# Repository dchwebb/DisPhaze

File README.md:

# Dis Phaze

Eurorack module providing two Phase Distortion oscillators based on Casio's CZ synthesizors. 

Phase distortion involves warping a sine wave using a second phase distortion signal. The phase distortion tables in this module were loosely based on waveforms sampled from a Casio CZ-1000. Both oscillators allow the sine wave to be warped by a greater amount than on the original and in the case of oscillator 1 the phase distortion tables can be continuously varied.

Functionality
-------------

Disphaze is a two channel design where each channel controls 5 phase distortion waves. These are used to change the playback rate of the audio wave which is always a sine wave. All of the PD waves are based on the CZ but some are generated mathematically, some literally sampled and converted from an original CZ-1000.

The module is duophonic – channel one has a bit more range and so can go more extreme than the CZ. Channel one allows the PD waves morph from one to the next. The second channel does not morph and has a more limited range so it is a bit more 'authentic'. Channel two can also be offset by an octave from channel one which is particularly useful for ring modulation. The module works well in stereo with the two channels split left and right.

Channel one has a Ring Mod switch which digitally multiplies both channel ouputs. Channel two has a mix switch which adds both channel outputs.

The amount of phase distortion applied can be controlled with a knob and/or CV input. Pitch is applied with a 1V/Octave input which is also normalled to the Doepfer standard 16 pin Eurorack connector. The module is also supplied with a VCA input - this allows the use of an envelope generator (or other CV source) to control volume without the need for an external VCA.

Calibration
-----------

 * Set fine tune and both phase distortion amount knobs to the center position
 * Connect a voltage source to the 1V/Oct input
 * Press the calibration button once (top right of back of PCB) - a square wave will be output on channel 1
 * The top left knob will adjust the tuning offset (will be affected by spread setting)
 * The top right knob will adjust the tuning spread (test by checking different octaves)
 * When the calibration is complete press the calibration button again to save

Technical
---------

The heart of the module is the STM32F405 microcontroller running at 168MHz. Timing is generated with an external 8MHz crystal oscillator. CV inputs are conditioned with an MCP6004 OpAmp. The outputs are derived from the Microcontroller's 12 bit DACs amplified via a TL072 OpAmp. The microcontroller is programmed from a 4 pin SWD header.

The module uses a two PCB sandwich construction with vertical potentiometers and jack sockets connecting the two PCBs and providing structural rigidity.
 
 Errata
 ------
 
 * On v2 of the PCB the BOOT0 pin (pin 60) is floating which causes problems programming and debugging over the SWD interface. A bodge wire connects this to ground (pin 2 of C9).
 * Silkscreen for C4 and C17 are incorrectly swapped
 * VDDA is missing decoupling capacitors
 * Reset button missing
 * USB/UART not exposed
 * No silkscreen on calibrate button

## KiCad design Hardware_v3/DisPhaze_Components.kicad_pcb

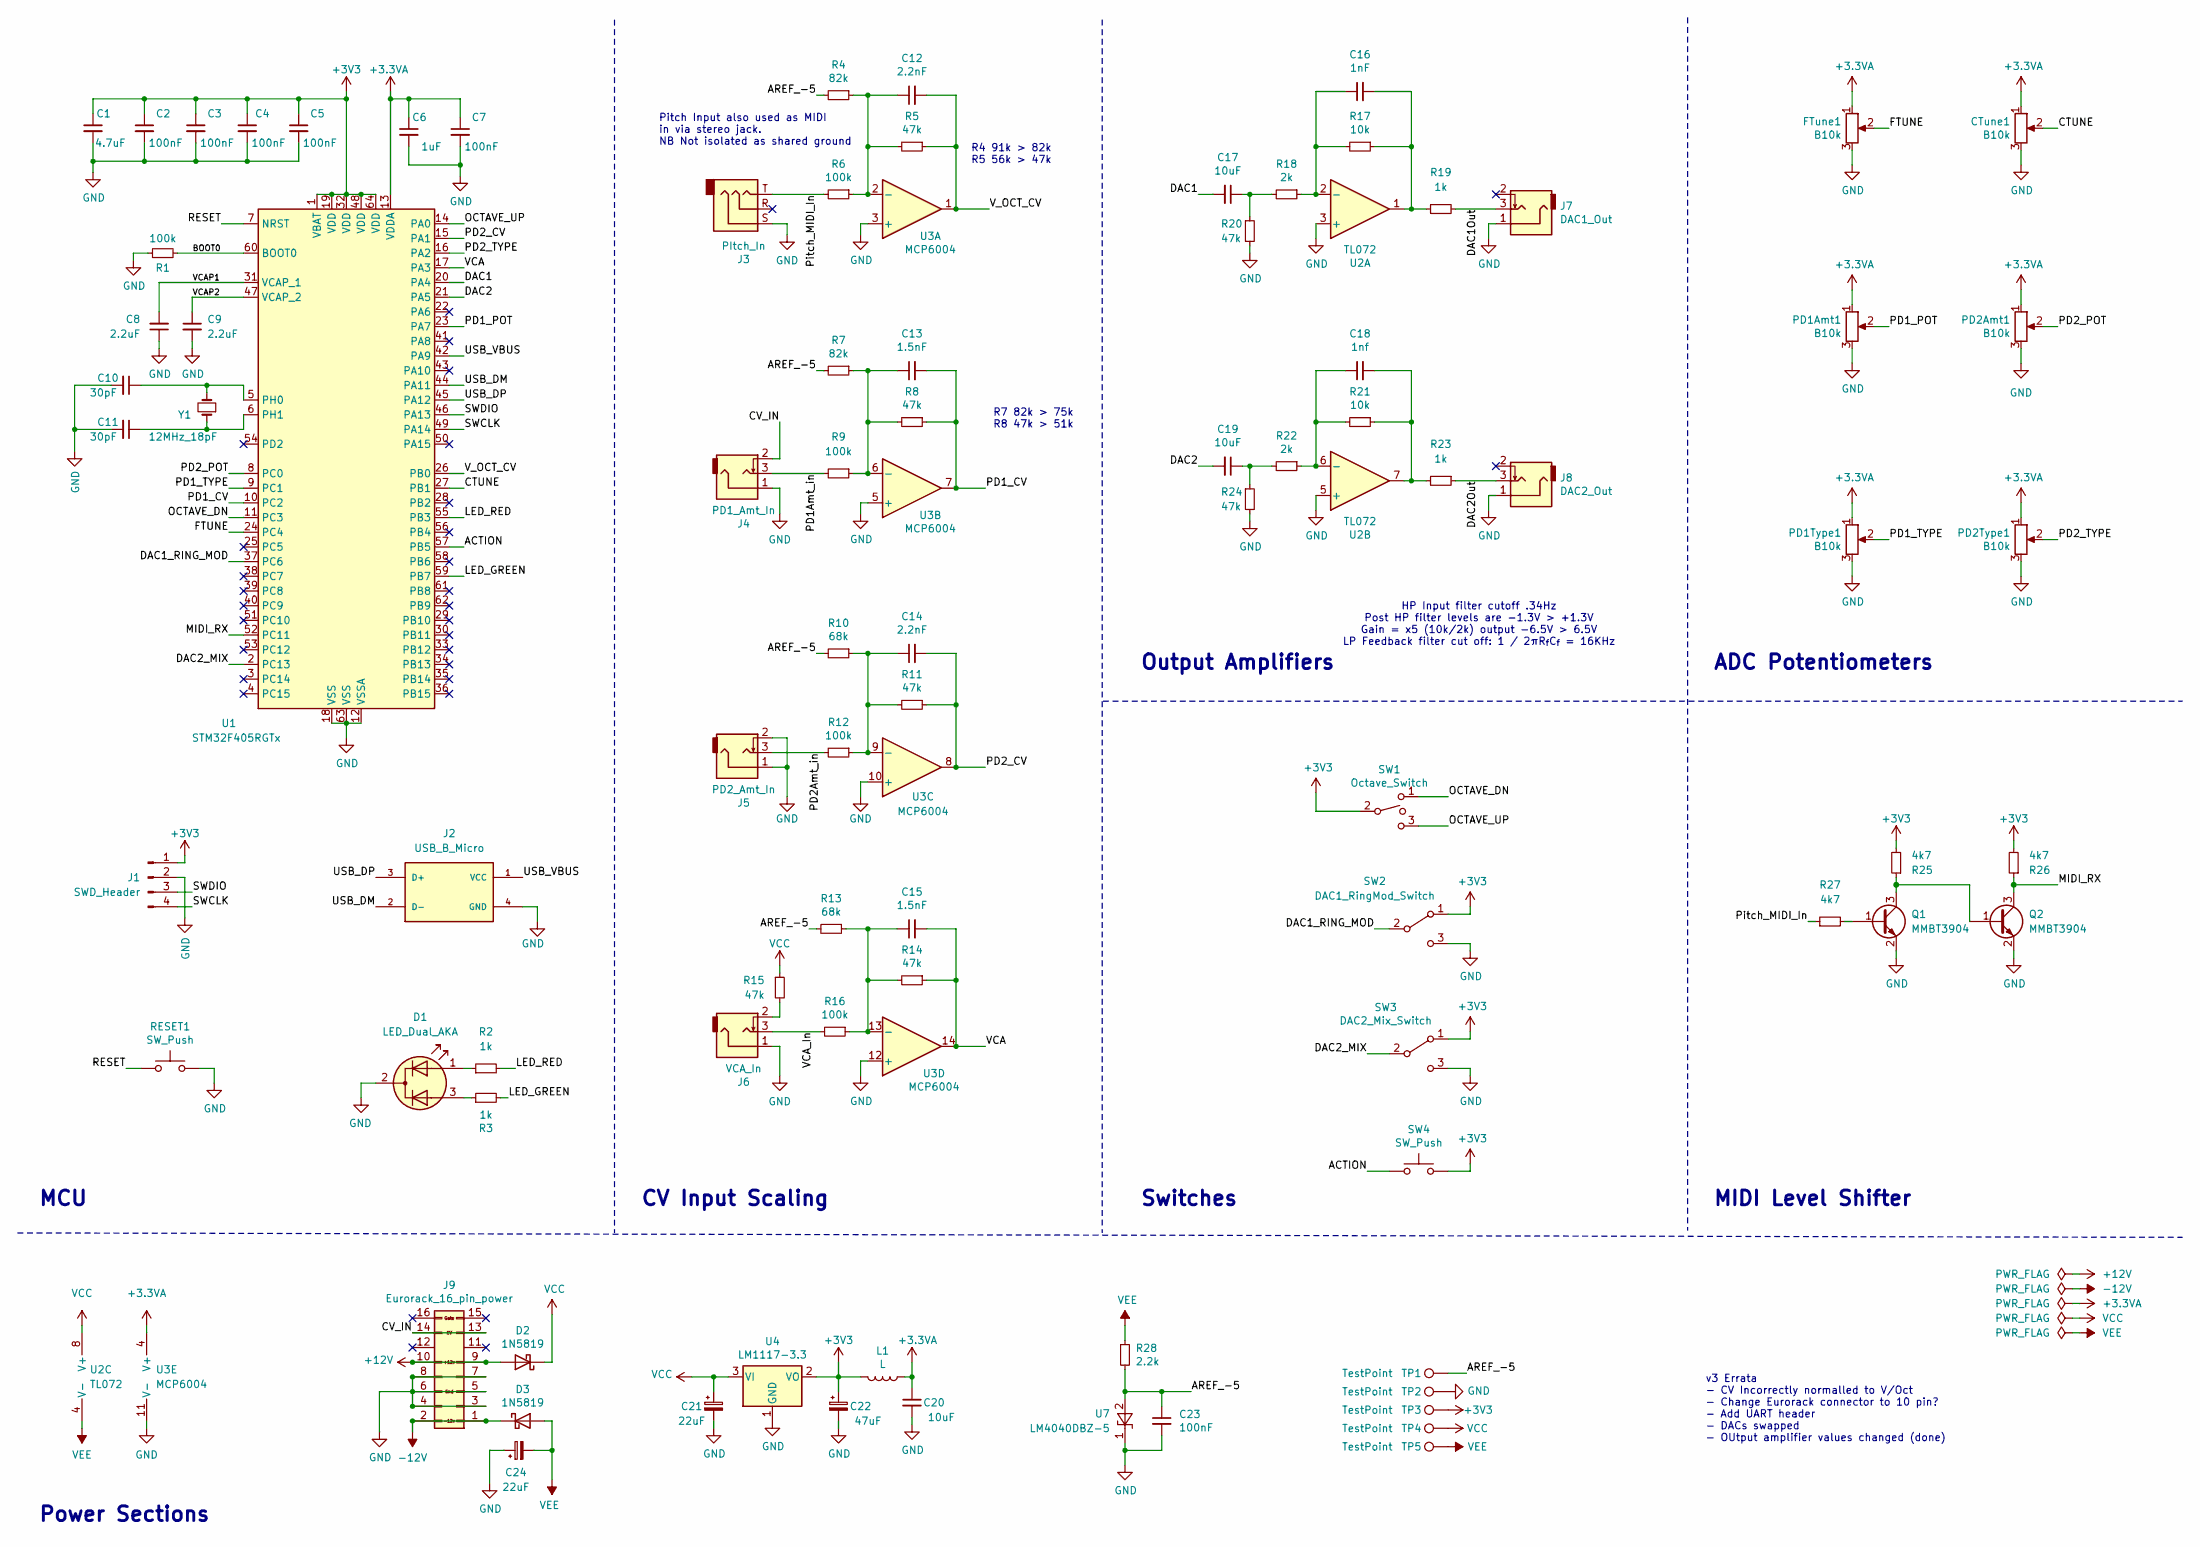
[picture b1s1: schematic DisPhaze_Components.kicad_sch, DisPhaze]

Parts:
C1: 4.7uF; C_0603_1608Metric
C2, C3, C4, C5, C7, C23: 100nF; C_0603_1608Metric
C6: 1uF; C_0603_1608Metric
C8, C9: 2.2uF; C_0603_1608Metric
C10, C11: 30pF; C_0603_1608Metric
C12, C14: 2.2nF; C_0603_1608Metric
C13, C15: 1.5nF; C_0603_1608Metric
C16: 1nF; C_0603_1608Metric
C17, C19: 10uF; C_0603_1608Metric
C18: 1nf; C_0603_1608Metric
C20: 10uF; C_0805_2012Metric
C21, C24: 22uF; CP_Elec_4x5.3
C22: 47uF; CP_Elec_5x5.4
CTune1: B10k; Alpha_9mm_Potentiometer_Aligned
D1: LED_Dual_AKA; LED_D3.0mm-3
D2, D3: 1N5819; D_SOD-123
FTune1: B10k; Alpha_9mm_Potentiometer_Aligned
J1: SWD_Header; SWD_header
J2: USB_B_Micro; USB_TE_1734517-1
J3: PItch_In; Thonkiconn_Stereo-PJ366ST
J4: PD1_Amt_In; THONKICONN_hole
J5: PD2_Amt_In; THONKICONN_hole
J6: VCA_In; THONKICONN_hole
J7: DAC1_Out; THONKICONN_hole
J8: DAC2_Out; THONKICONN_hole
J9: Eurorack_16_pin_power; Eurorack_16_pin_header
L1: L; L_0805_2012Metric
PD1Amt1, PD1Type1, PD2Amt1, PD2Type1: B10k; Alpha_9mm_Potentiometer_Aligned
Q1, Q2: MMBT3904; SOT-23; Part_Number C20526
R1: 100k; R_0603_1608Metric; Part_Number C25803
R2, R3, R19, R23: 1k; R_0603_1608Metric
R4, R7: 82k; R_0603_1608Metric
R5, R8, R11, R14, R15, R20, R24: 47k; R_0603_1608Metric
R6, R9, R12, R16: 100k; R_0603_1608Metric
R10, R13: 68k; R_0603_1608Metric
R17, R21: 10k; R_0603_1608Metric
R18, R22: 2k; R_0603_1608Metric
R25, R26, R27: 4k7; R_0603_1608Metric; Part_Number C23162
R28: 2.2k; R_0603_1608Metric
RESET1: SW_Push; SW_SPST_EVQQ2
SW1: Octave_Switch; SPDTSubMiniature
SW2: DAC1_RingMod_Switch; SPDTSubMiniature
SW3: DAC2_Mix_Switch; SPDTSubMiniature
SW4: SW_Push; SW_PUSH_6mm_aligned
TP1, TP2, TP3, TP4, TP5: TestPoint; 1.3mm_Test_Point
U1: STM32F405RGTx; LQFP-64_10x10mm_P0.5mm
U2: TL072; SOIC-8_3.9x4.9mm_P1.27mm
U3: MCP6004; SOIC-14_3.9x8.7mm_P1.27mm
U4: LM1117-3.3; SOT-223-3_TabPin2
U7: LM4040DBZ-5; SOT-23
Y1: 12MHz_18pF; Crystal_SMD_0603-2Pin_6.0x3.5mm

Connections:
+3.3VA: C6.1, C7.1, C20.1, CTune1.1, FTune1.1, L1.1, PD1Amt1.1, PD1Type1.1, PD2Amt1.1, PD2Type1.1, U1.13 (VDDA), U3.4 (V+)
+3V3: C1.1, C2.1, C3.1, C4.1, C5.1, C22.1, J1.1, L1.2, R25.2, R26.2, SW1.2, SW2.1 (A), SW3.1 (A), SW4.2, TP3.1, U1.1 (VBAT), U1.19 (VDD), U1.32 (VDD), U1.48 (VDD), U1.64 (VDD), U4.2 (VO)
+12V: D2.2 (A), J9.9, J9.10
-12V: D3.1 (K), J9.1, J9.2
/ACTION: SW4.1, U1.57 (PB5)
/AREF_-5: C23.1, R4.2, R7.2, R10.2, R13.2, R28.2, TP1.1, U7.2 (A)
/BOOT0: R1.2, U1.60 (BOOT0)
/CTUNE: CTune1.2, U1.27 (PB1)
/CV_IN: J4.2, J9.13, J9.14
/DAC1: C17.2, U1.20 (PA4)
/DAC1Out: J7.3, R19.2
/DAC1_RING_MOD: SW2.2 (B), U1.37 (PC6)
/DAC2: C19.2, U1.21 (PA5)
/DAC2Out: J8.3, R23.1
/DAC2_MIX: SW3.2 (B), U1.2 (PC13)
/FTUNE: FTune1.2, U1.24 (PC4)
/LED_GREEN: R3.2, U1.59 (PB7)
/LED_RED: R2.2, U1.55 (PB3)
/MIDI_RX: Q2.3 (C), R26.1, U1.52 (PC11)
/OCTAVE_DN: SW1.1, U1.11 (PC3)
/OCTAVE_UP: SW1.3, U1.14 (PA0)
/PD1Amt_in: J4.3, R9.2
/PD1_CV: C13.2, R8.1, U1.10 (PC2), U3.7
/PD1_POT: PD1Amt1.2, U1.23 (PA7)
/PD1_TYPE: PD1Type1.2, U1.9 (PC1)
/PD2Amt_in: J5.3, R12.2
/PD2_CV: C14.2, R11.1, U1.15 (PA1), U3.8
/PD2_POT: PD2Amt1.2, U1.8 (PC0)
/PD2_TYPE: PD2Type1.2, U1.16 (PA2)
/Pitch_MIDI_In: J3.T, R6.2, R27.1
/RESET: RESET1.1, U1.7 (NRST)
/SWCLK: J1.4, U1.49 (PA14)
/SWDIO: J1.3, U1.46 (PA13)
/USB_DM: J2.2 (D-), U1.44 (PA11)
/USB_DP: J2.3 (D+), U1.45 (PA12)
/USB_VBUS: J2.1 (VCC), U1.42 (PA9)
/VCA: C15.2, R14.1, U1.17 (PA3), U3.14
/VCAP1: C8.2, U1.31 (VCAP_1)
/VCAP2: C9.1, U1.47 (VCAP_2)
/VCA_In: J6.3, R16.2
/V_OCT_CV: C12.2, R5.1, U1.26 (PB0), U3.1
GND: C1.2, C2.2, C3.2, C4.2, C5.2, C6.2, C7.2, C8.1, C9.2, C10.2, C11.2, C20.2, C21.2, C22.2, C23.2, C24.1, CTune1.3, D1.2 (K), FTune1.3, J1.2, J2.4 (GND), J3.S, J4.1, J5.1, J5.2, J6.1, J7.1, J8.1, J9.3, J9.4, J9.5, J9.6, J9.7, J9.8, PD1Amt1.3, PD1Type1.3, PD2Amt1.3, PD2Type1.3, Q1.2 (E), Q2.2 (E), R1.1, R20.2, R24.2, RESET1.2, SW2.3 (C), SW3.3 (C), TP2.1, U1.12 (VSSA), U1.18 (VSS), U1.63 (VSS), U2.3 (+), U2.5 (+), U3.3 (+), U3.5 (+), U3.10 (+), U3.11 (V-), U3.12 (+), U4.1 (GND), U7.1 (K)
unnamed: C10.1, U1.5 (PH0), Y1.2
unnamed: C11.1, U1.6 (PH1), Y1.1
unnamed: C12.1, R4.1, R5.2, R6.1, U3.2 (-)
unnamed: C13.1, R7.1, R8.2, R9.1, U3.6 (-)
unnamed: C14.1, R10.1, R11.2, R12.1, U3.9 (-)
unnamed: C15.1, R13.1, R14.2, R16.1, U3.13 (-)
unnamed: C16.1, R17.2, R18.1, U2.2 (-)
unnamed: C16.2, R17.1, R19.1, U2.1
unnamed: C17.1, R18.2, R20.1
unnamed: C18.1, R21.2, R22.1, U2.6 (-)
unnamed: C18.2, R21.1, R23.2, U2.7
unnamed: C19.1, R22.2, R24.1
unnamed: D1.1 (A1), R2.1
unnamed: D1.3 (A2), R3.1
unnamed: J6.2, R15.2
unnamed: Q1.1 (B), R27.2
unnamed: Q1.3 (C), Q2.1 (B), R25.1
VCC: C21.1, D2.1 (K), R15.1, TP4.1, U2.8 (V+), U4.3 (VI)
VEE: C24.2, D3.2 (A), R28.1, TP5.1, U2.4 (V-)

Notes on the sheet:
CV Input Scaling
v3 Errata - CV Incorrectly normalled to V/Oct - Change Eurorack connector to 10 pin? - Add UART header - DACs swapped - OUtput amplifier values changed (done)
Output Amplifiers
ADC Potentiometers
Pitch Input also used as MIDI in via stereo jack. NB Not isolated as shared ground
MCU
R7 82k > 75k R8 47k > 51k
Power Sections
Switches
R4 91k > 82k R5 56k > 47k
HP Input filter cutoff .34Hz Post HP filter levels are -1.3V > +1.3V Gain = x5 (10k/2k) output -6.5V > 6.5V LP Feedback filter cut off: 1 / 2πR_{f}C_{f} = 16KHz
MIDI Level Shifter

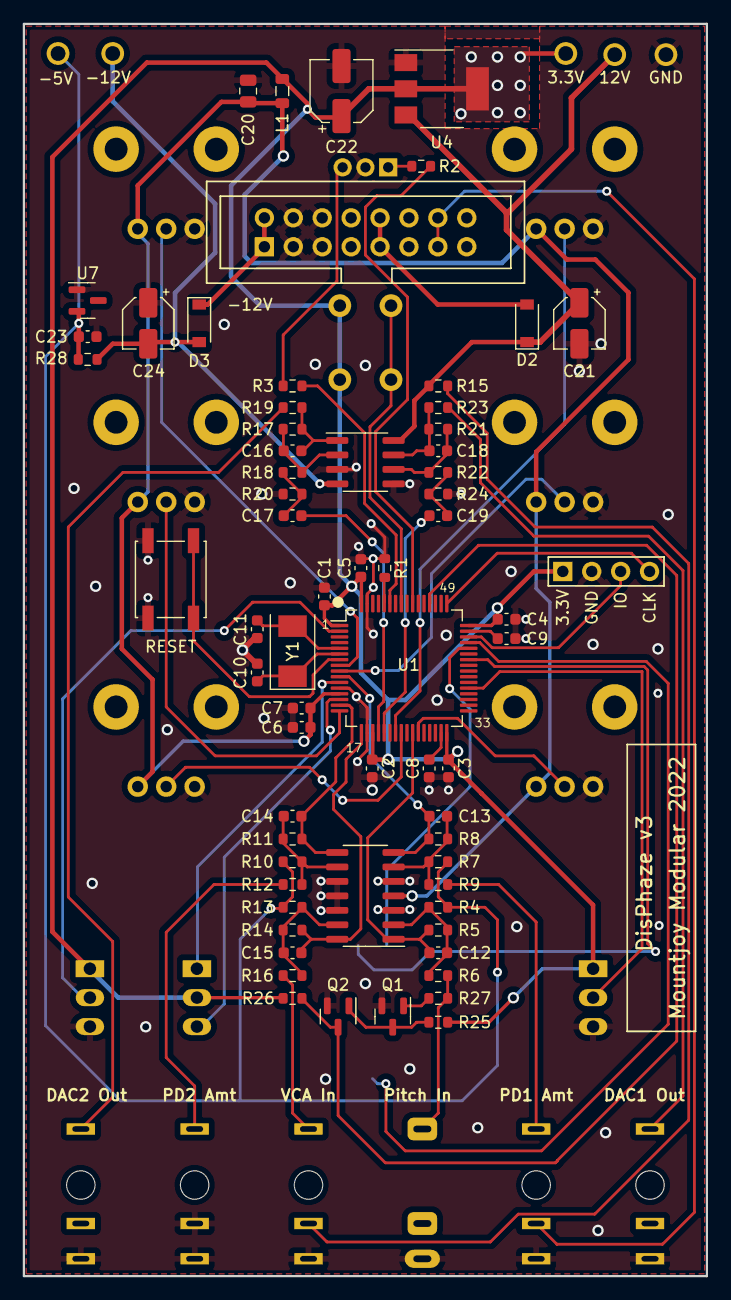
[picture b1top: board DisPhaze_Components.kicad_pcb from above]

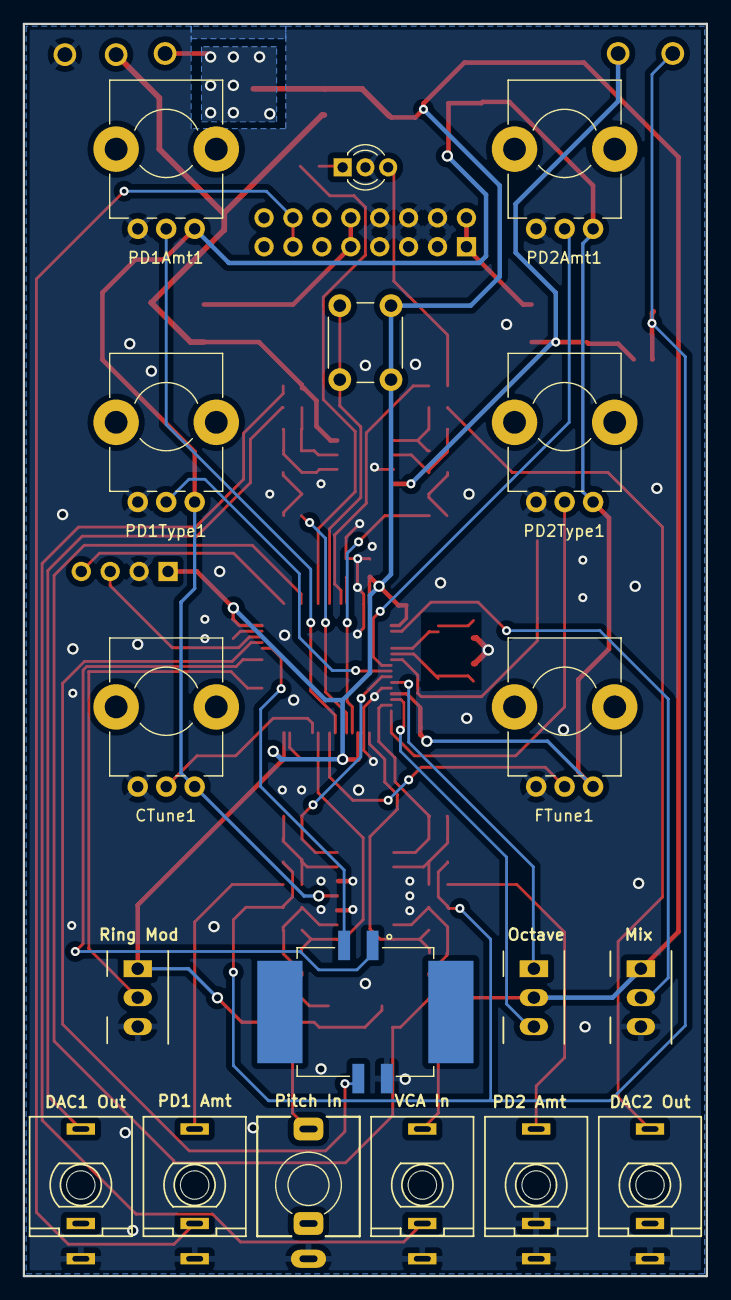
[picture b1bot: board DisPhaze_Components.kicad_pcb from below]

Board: 2 copper layers, 60.0 x 110.0 mm, 89 parts (18 on the bottom side), 61 nets.

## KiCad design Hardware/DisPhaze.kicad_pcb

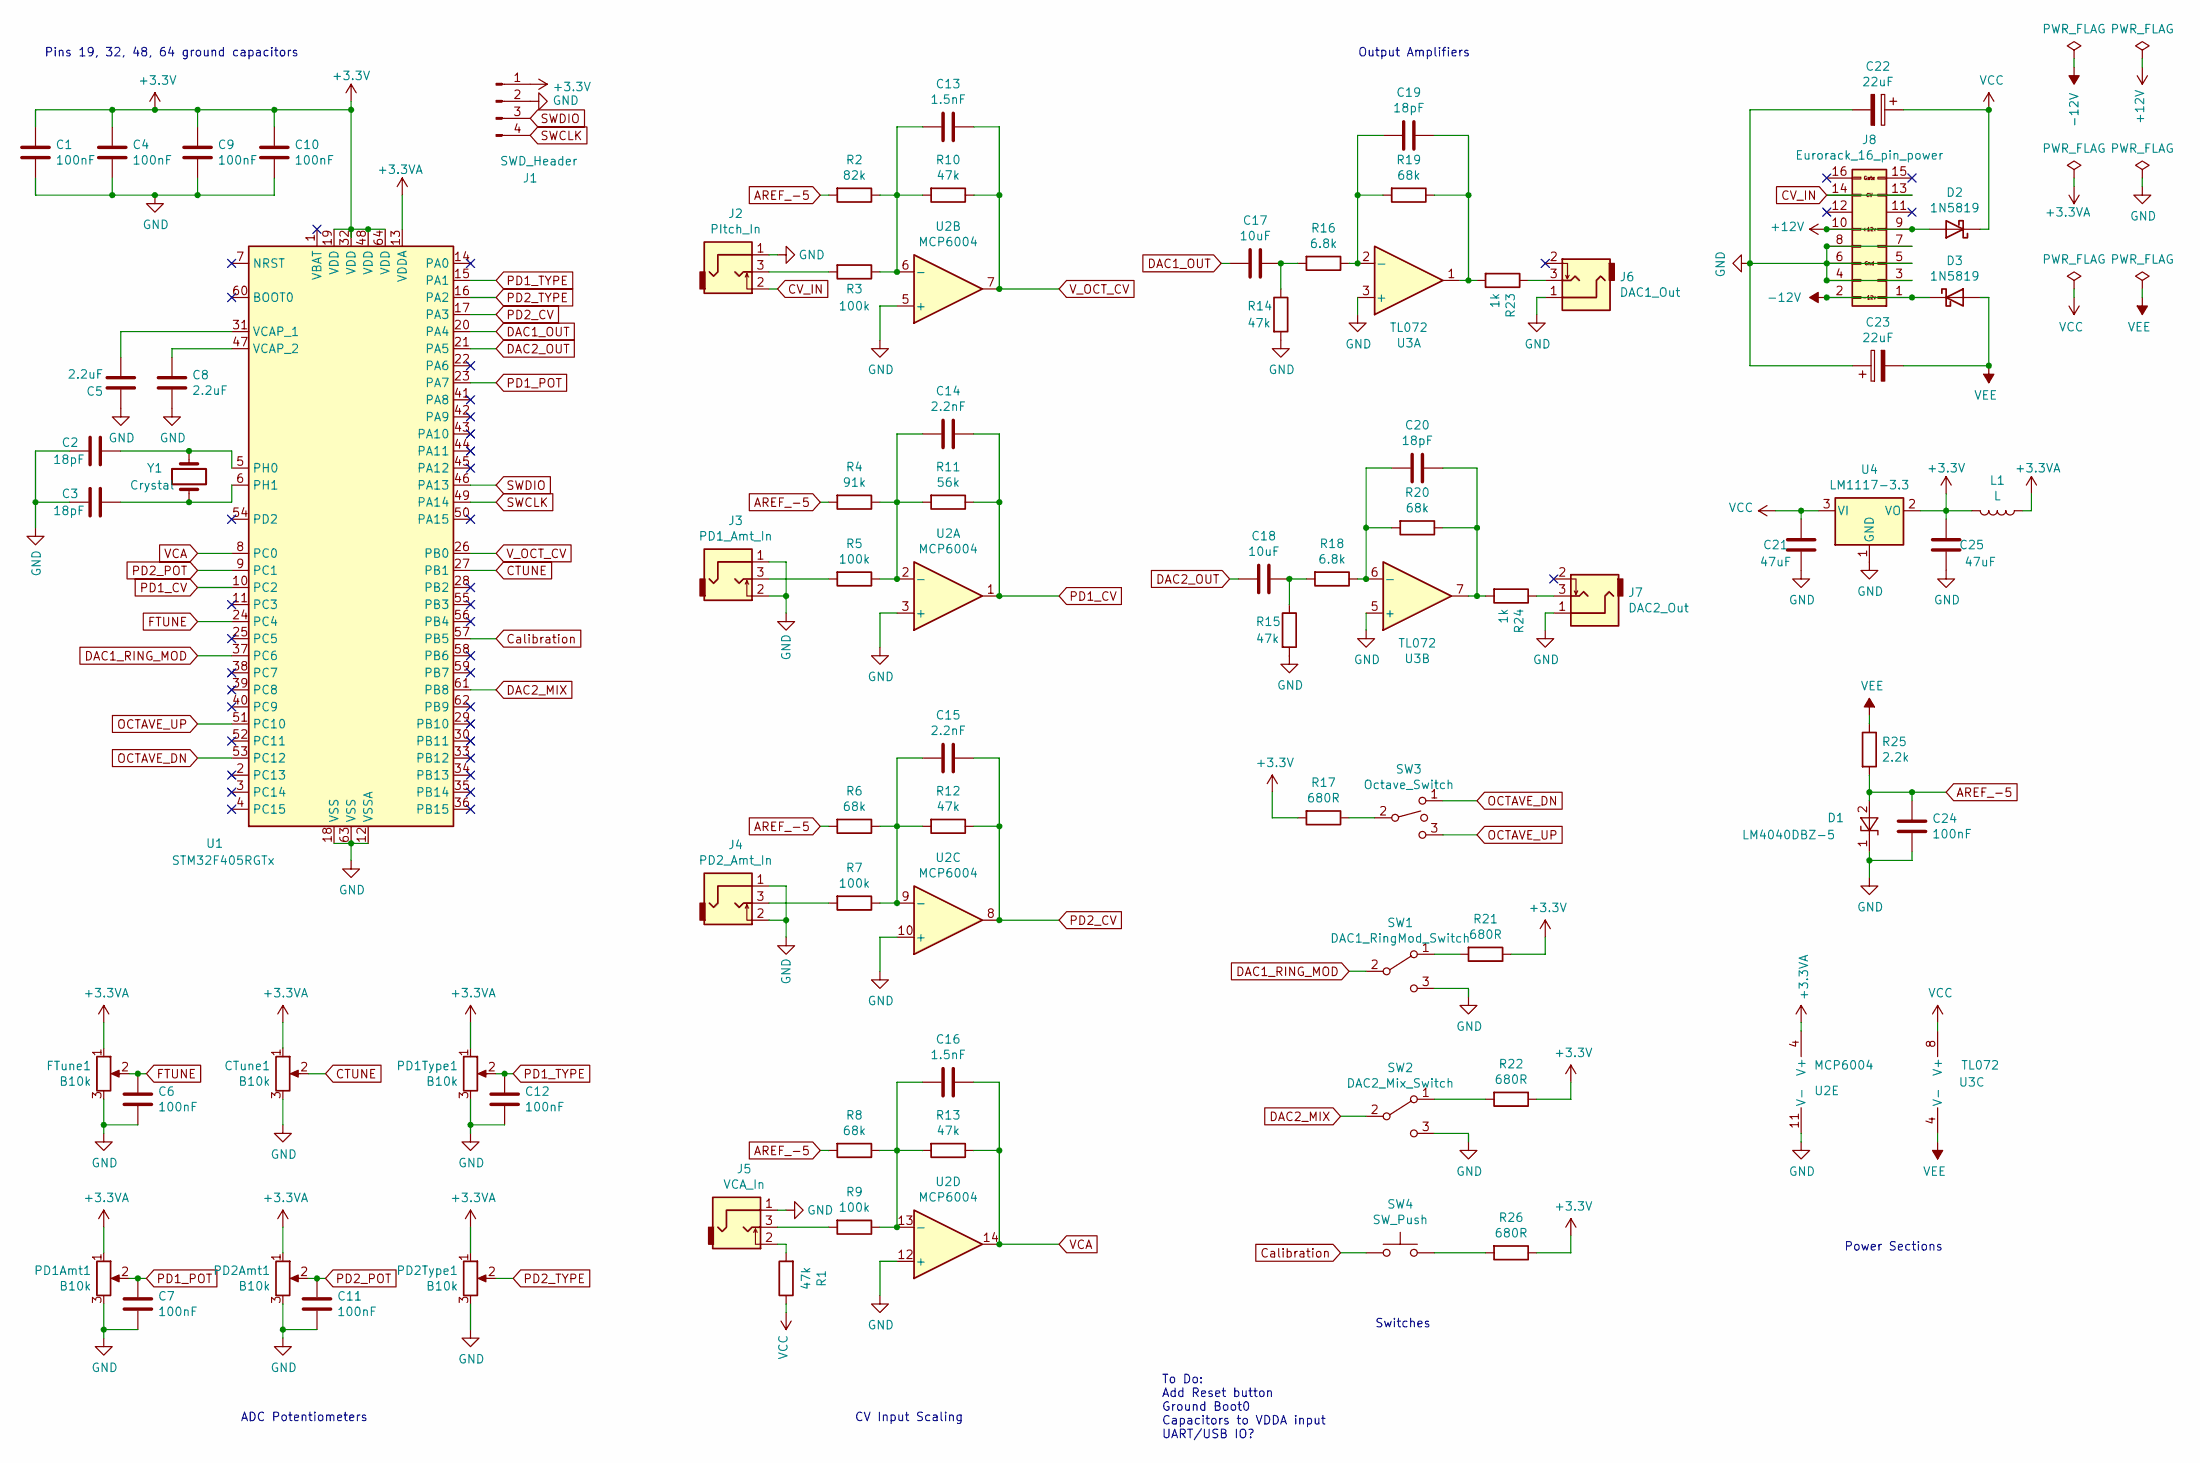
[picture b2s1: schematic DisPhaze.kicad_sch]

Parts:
C1, C4, C6, C7, C9, C10, C11, C12, C24: 100nF; C_0805_HandSoldering
C2, C3, C19, C20: 18pF; C_0805_HandSoldering
C5, C8: 2.2uF; C_0805_HandSoldering
C13, C16: 1.5nF; C_0805_HandSoldering
C14, C15: 2.2nF; C_0805_HandSoldering
C17, C18: 10uF; C_0805_HandSoldering
C21, C25: 47uF; CP_Elec_5x5.8
C22, C23: 22uF; CP_Elec_4x5.8
CTune1: B10k; Alpha_9mm_Potentiometer
D1: LM4040DBZ-5; SOT-23
D2, D3: 1N5819; D_SOD-123
FTune1: B10k; Alpha_9mm_Potentiometer
J1: SWD_Header; SWD_header
J2: PItch_In; THONKICONN_hole
J3: PD1_Amt_In; THONKICONN_hole
J4: PD2_Amt_In; THONKICONN_hole
J5: VCA_In; THONKICONN_hole
J6: DAC1_Out; THONKICONN_hole
J7: DAC2_Out; THONKICONN_hole
J8: Eurorack_16_pin_power; Eurorack_16_pin_header
L1: L; R_0805_HandSoldering
PD1Amt1, PD1Type1, PD2Amt1, PD2Type1: B10k; Alpha_9mm_Potentiometer
R1, R10, R12, R13, R14, R15: 47k; R_0805_HandSoldering
R2: 82k; R_0805_HandSoldering
R3, R5, R7, R9: 100k; R_0805_HandSoldering
R4: 91k; R_0805_HandSoldering
R6, R8, R19, R20: 68k; R_0805_HandSoldering
R11: 56k; R_0805_HandSoldering
R16, R18: 6.8k; R_0805_HandSoldering
R17, R21, R22, R26: 680R; R_0805_HandSoldering
R23, R24: 1k; R_0805_HandSoldering
R25: 2.2k; R_0805_HandSoldering
SW1: DAC1_RingMod_Switch; SPDTSubMiniature
SW2: DAC2_Mix_Switch; SPDTSubMiniature
SW3: Octave_Switch; SPDTSubMiniature
SW4: SW_Push; SW_SPST_EVQQ2
U1: STM32F405RGTx; LQFP-64_10x10mm_P0.5mm
U2: MCP6004; SOIC-14_N
U3: TL072; SOIC-8-N
U4: LM1117-3.3; TO-252-3_TabPin2
Y1: Crystal; Crystal_SMD

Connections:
+3.3VA: CTune1.1, FTune1.1, L1.1, PD1Amt1.1, PD1Type1.1, PD2Amt1.1, PD2Type1.1, U1.13 (VDDA), U2.4 (V+)
+3V3: C1.1, C4.1, C9.1, C10.1, C25.1, J1.1, L1.2, R17.2, R21.1, R22.1, R26.1, U1.19 (VDD), U1.32 (VDD), U1.48 (VDD), U1.64 (VDD), U4.2 (VO)
+12V: D2.2 (A), J8.9, J8.10
-12V: D3.1 (K), J8.1, J8.2
AREF_-5: C24.1, D1.2 (A), R2.2, R4.2, R6.2, R8.2, R25.2
CTUNE: CTune1.2, U1.27 (PB1)
CV_IN: J2.2, J8.13, J8.14
Calibration: SW4.1, U1.57 (PB5)
DAC1_OUT: C17.2, U1.20 (PA4)
DAC1_RING_MOD: SW1.2 (B), U1.37 (PC6); also elsewhere on the board
DAC2_MIX: SW2.2 (B), U1.61 (PB8)
DAC2_OUT: C18.2, U1.21 (PA5)
FTUNE: C6.1, FTune1.2, U1.24 (PC4)
GND: C1.2, C2.2, C3.2, C4.2, C5.1, C6.2, C7.2, C8.2, C9.2, C10.2, C11.2, C12.2, C21.2, C22.2, C23.1, C24.2, C25.2, CTune1.3, D1.1 (K), FTune1.3, J1.2, J2.1, J3.1, J3.2, J4.1, J4.2, J5.1, J6.1, J7.1, J8.3, J8.4, J8.5, J8.6, J8.7, J8.8, PD1Amt1.3, PD1Type1.3, PD2Amt1.3, PD2Type1.3, R14.2, R15.2, SW1.3 (C), SW2.3 (C), U1.12 (VSSA), U1.18 (VSS), U1.63 (VSS), U2.3 (+), U2.5 (+), U2.10 (+), U2.11 (V-), U2.12 (+), U3.3 (+), U3.5 (+), U4.1 (GND); also elsewhere on the board
unnamed: C2.1, U1.5 (PH0), Y1.2
unnamed: C3.1, U1.6 (PH1), Y1.1
unnamed: C5.2, U1.31 (VCAP_1)
unnamed: C8.1, U1.47 (VCAP_2)
unnamed: C13.1, R2.1, R3.1, R10.2, U2.6 (-)
unnamed: C14.1, R4.1, R5.1, R11.2, U2.2 (-)
unnamed: C15.1, R6.1, R7.1, R12.2, U2.9 (-)
unnamed: C16.1, R8.1, R9.1, R13.2, U2.13 (-)
unnamed: C17.1, R14.1, R16.2
unnamed: C18.1, R15.1, R18.2
unnamed: C19.1, R16.1, R19.2, U3.2 (-)
unnamed: C19.2, R19.1, R23.2, U3.1
unnamed: C20.1, R18.1, R20.2, U3.6 (-)
unnamed: C20.2, R20.1, R24.2, U3.7
unnamed: J2.3, R3.2
unnamed: J3.3, R5.2
unnamed: J4.3, R7.2
unnamed: J5.2, R1.2
unnamed: J5.3, R9.2
unnamed: J6.3, R23.1
unnamed: J7.3, R24.1
unnamed: R17.1, SW3.2
unnamed 42: R21.2, SW1.1 (A); also elsewhere on the board
unnamed: R22.2, SW2.1 (A)
unnamed: R26.2, SW4.2
OCTAVE_DN: SW3.1, U1.53 (PC12)
OCTAVE_UP: SW3.3, U1.51 (PC10)
PD1_CV: C14.2, R11.1, U1.10 (PC2), U2.1
PD1_POT: C7.1, PD1Amt1.2, U1.23 (PA7)
PD1_TYPE: C12.1, PD1Type1.2, U1.15 (PA1)
PD2_CV: C15.2, R12.1, U1.17 (PA3), U2.8
PD2_POT: C11.1, PD2Amt1.2, U1.9 (PC1)
PD2_TYPE: PD2Type1.2, U1.16 (PA2)
SWCLK: J1.4, U1.49 (PA14)
SWDIO: J1.3, U1.46 (PA13)
VCA: C16.2, R13.1, U1.8 (PC0), U2.14
VCC: C21.1, C22.1, D2.1 (K), R1.1, U3.8 (V+), U4.3 (VI)
VEE: C23.2, D3.2 (A), R25.1, U3.4 (V-)
V_OCT_CV: C13.2, R10.1, U1.26 (PB0), U2.7

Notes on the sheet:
CV Input Scaling
To Do: Add Reset button Ground Boot0 Capacitors to VDDA input UART/USB IO?
Pins 19, 32, 48, 64 ground capacitors
Output Amplifiers
ADC Potentiometers
Power Sections
Switches

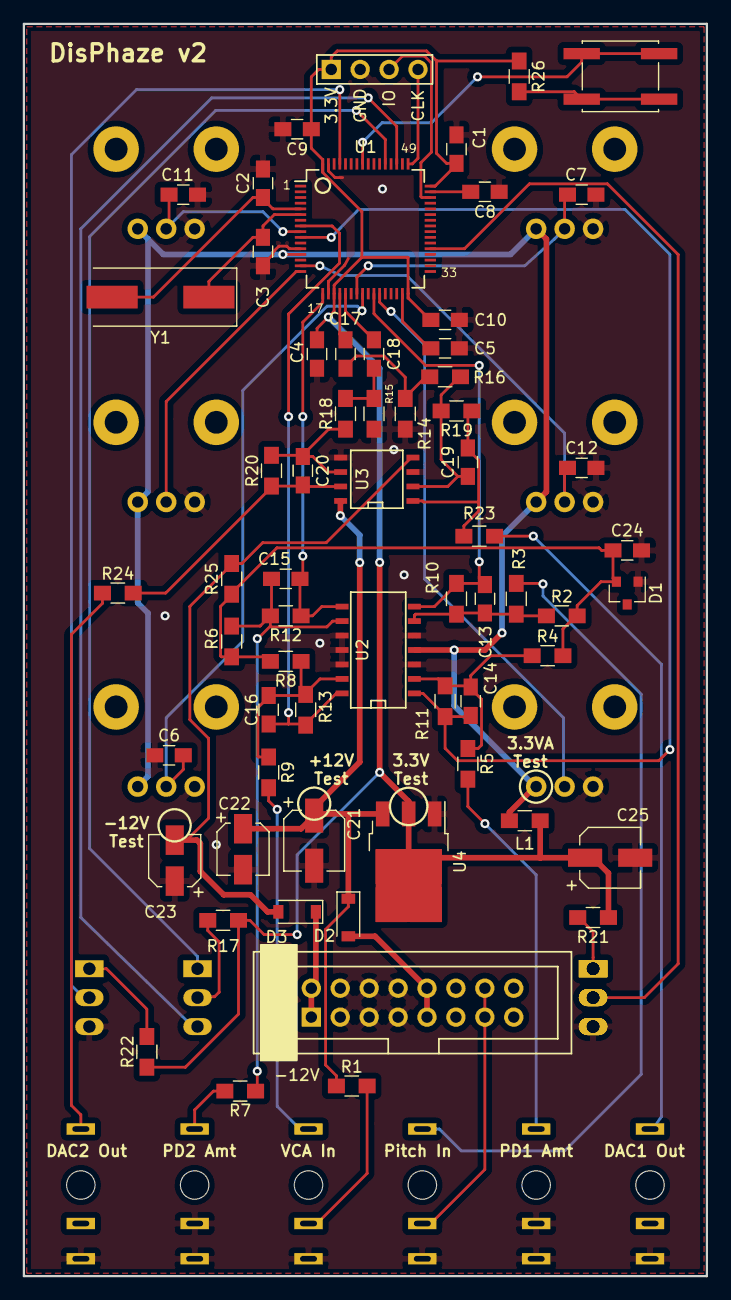
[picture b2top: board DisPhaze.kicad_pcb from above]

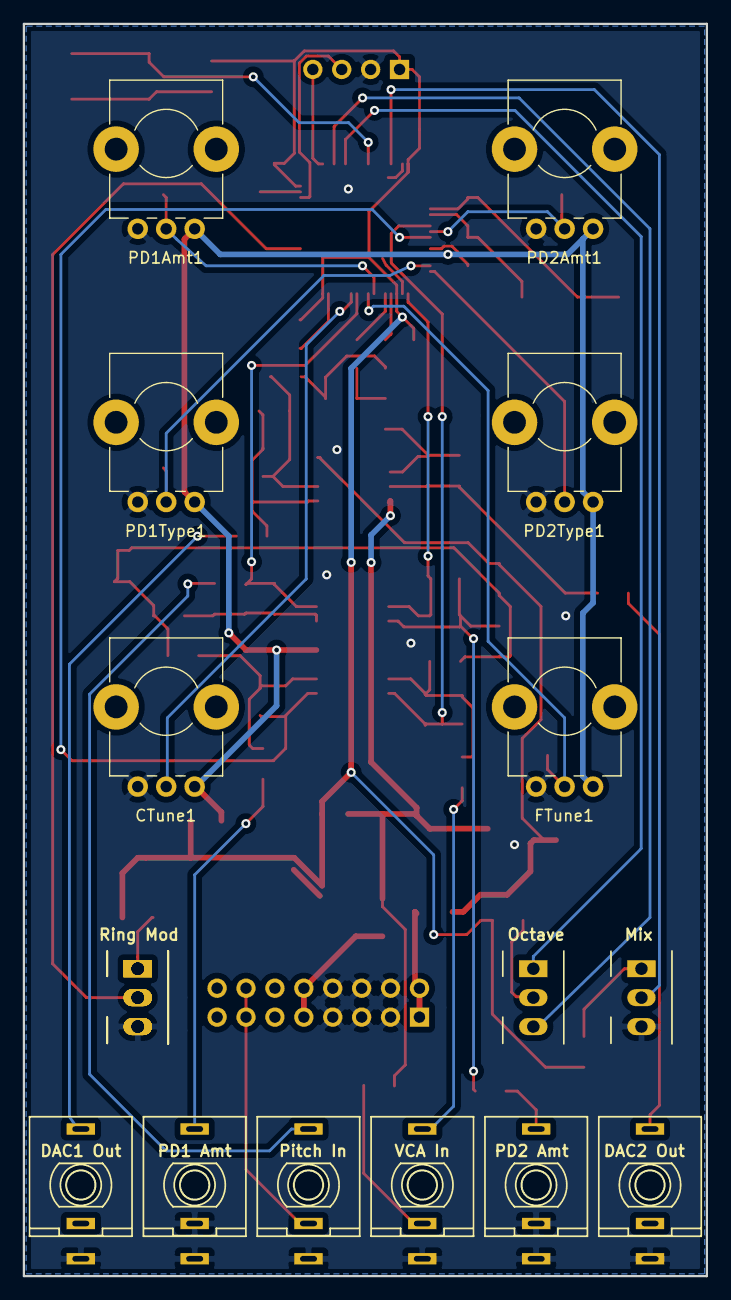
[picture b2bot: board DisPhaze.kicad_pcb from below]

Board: 2 copper layers, 60.0 x 110.0 mm, 80 parts (17 on the bottom side), 53 nets.

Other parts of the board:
SW1#2, SW1#3: DAC1_RingMod_Switch; SPDTSubMiniature

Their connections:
DAC1_RING_MOD: SW1#2.2, SW1#3.2; also elsewhere on the board
GND: SW1#2.3, SW1#3.3; also elsewhere on the board
unnamed 42: SW1#2.1, SW1#3.1; also elsewhere on the board

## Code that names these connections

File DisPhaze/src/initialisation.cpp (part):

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
void InitDAC()
{
	// Once the DAC channelx is enabled, the corresponding GPIO pin (PA4 or PA5) is automatically connected to the analog converter output (DAC_OUTx).
	// In order to avoid parasitic consumption, the PA4 or PA5 pin should first be configured to analog (AIN).

	// Enable DAC and GPIO Clock
	RCC->AHB1ENR |= RCC_AHB1ENR_GPIOAEN;			// Enable GPIO Clock
	RCC->APB1ENR |= RCC_APB1ENR_DACEN;				// Enable DAC Clock

	DAC->CR |= DAC_CR_EN1;							// Enable DAC using PA4 (DAC_OUT1)
	DAC->CR |= DAC_CR_BOFF1;						// Enable DAC channel output buffer to reduce the output impedance
	DAC->CR |= DAC_CR_TEN1;							// DAC 1 enable trigger
	DAC->CR |= DAC_CR_TSEL1;						// Set trigger to software (0b111: Software trigger)

	DAC->CR |= DAC_CR_EN2;							// Enable DAC using PA5 (DAC_OUT2)
	DAC->CR |= DAC_CR_BOFF2;						// Enable DAC channel output buffer
	DAC->CR |= DAC_CR_TEN2;							// DAC 2 enable trigger
	DAC->CR |= DAC_CR_TSEL2;						// Set trigger to software (0b111: Software trigger)
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	RCC->AHB1ENR |= RCC_AHB1ENR_GPIOCEN;			// reset and clock control - advanced high performance bus - GPIO port C
	RCC->APB2ENR |= RCC_APB2ENR_SYSCFGEN;			// Enable system configuration clock: used to manage external interrupt line connection to GPIOs

	// PC6 Ring Mod Button in
	GPIOC->MODER &= ~(GPIO_MODER_MODER6);			// input mode is default
	GPIOC->PUPDR |= GPIO_PUPDR_PUPDR6_0;			// Set pin to pull up:  01 Pull-up; 10 Pull-down; 11 Reserved

	// PB8 DAC2 Mix mode switch
	GPIOB->MODER &= ~(GPIO_MODER_MODER8);			// input mode is default
	GPIOB->PUPDR |= GPIO_PUPDR_PUPDR8_1;			// Set pin to pull down:  01 Pull-up; 10 Pull-down; 11 Reserved

	// PB5 Calibration button
	GPIOB->MODER &= ~(GPIO_MODER_MODER5);			// input mode is default
	GPIOB->PUPDR |= GPIO_PUPDR_PUPDR5_1;			// Set pin to pull up:  01 Pull-up; 10 Pull-down; 11 Reserved

	// Set up PC10 and PC12 for octave up and down switch

	GPIOC->MODER |= GPIO_MODER_MODER10_0;			// Debug

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	GPIOC->PUPDR |= GPIO_PUPDR_PUPDR10_1;			// Set pin to pull down:  01 Pull-up; 10 Pull-down; 11 Reserved
	GPIOC->PUPDR |= GPIO_PUPDR_PUPDR12_1;			// Set pin to pull down:  01 Pull-up; 10 Pull-down; 11 Reserved

	// configure PB8 switch to fire on an interrupt (mix)
	SYSCFG->EXTICR[2] |= SYSCFG_EXTICR3_EXTI8_PB;	// Select Pin PB8 which uses External interrupt 3
	EXTI->RTSR |= EXTI_RTSR_TR8;					// Enable rising edge trigger for line 8
	EXTI->FTSR |= EXTI_FTSR_TR8;					// Enable falling edge trigger for line 8
	EXTI->IMR |= EXTI_IMR_MR8;						// Activate interrupt using mask register 8

	// configure PC6 switch to fire on an interrupt (ring mod)
	SYSCFG->EXTICR[1] |= SYSCFG_EXTICR2_EXTI6_PC;	// Select Pin PC6 which uses External interrupt 2
	EXTI->RTSR |= EXTI_RTSR_TR6;					// Enable rising edge trigger for line 6
	EXTI->FTSR |= EXTI_FTSR_TR6;					// Enable falling edge trigger for line 6
	EXTI->IMR |= EXTI_IMR_MR6;						// Activate interrupt using mask register 6
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	NVIC_SetPriority(EXTI9_5_IRQn, 3);
	NVIC_EnableIRQ(EXTI9_5_IRQn);

	// configure PC10 & PC12 switch to fire on an interrupt
	SYSCFG->EXTICR[2] |= SYSCFG_EXTICR3_EXTI10_PC;	// Select Pin PC10 which uses External interrupt 3
	EXTI->RTSR |= EXTI_RTSR_TR10;					// Enable rising edge trigger for line 10
	EXTI->FTSR |= EXTI_FTSR_TR10;					// Enable falling edge trigger for line 10
	EXTI->IMR |= EXTI_IMR_MR10;						// Activate interrupt using mask register 10

	SYSCFG->EXTICR[3] |= SYSCFG_EXTICR4_EXTI12_PC;	// Select Pin PC12 which uses External interrupt 4
	EXTI->RTSR |= EXTI_RTSR_TR12;					// Enable rising edge trigger for line 12
	EXTI->FTSR |= EXTI_FTSR_TR12;					// Enable falling edge trigger for line 12
	EXTI->IMR |= EXTI_IMR_MR12;						// Activate interrupt using mask register 12
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	RCC->APB2ENR |= RCC_APB2ENR_ADC1EN;


	GPIOB->MODER |= GPIO_MODER_MODER0;				// Set PB0 to Analog mode (0b11) ADC12_IN8
	GPIOB->MODER |= GPIO_MODER_MODER1;				// Set PB1 to Analog mode (0b11)
	GPIOA->MODER |= GPIO_MODER_MODER1;				// Set PA1 to Analog mode (0b11)
	GPIOA->MODER |= GPIO_MODER_MODER2;				// Set PA2 to Analog mode (0b11)
	GPIOA->MODER |= GPIO_MODER_MODER3;				// Set PA3 to Analog mode (0b11)
	GPIOC->MODER |= GPIO_MODER_MODER0;				// Set PC0 to Analog mode (0b11)
	GPIOC->MODER |= GPIO_MODER_MODER2;				// Set PC2 to Analog mode (0b11)
	GPIOC->MODER |= GPIO_MODER_MODER4;				// Set PC4 to Analog mode (0b11)
	GPIOA->MODER |= GPIO_MODER_MODER7;				// Set PA7 to Analog mode (0b11)
	GPIOC->MODER |= GPIO_MODER_MODER1;				// Set PA7 to Analog mode (0b11)


	ADC1->CR1 |= ADC_CR1_SCAN;						// Activate scan mode
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	RCC->AHB1ENR |= RCC_AHB1ENR_GPIOCEN;
	RCC->APB2ENR |= RCC_APB2ENR_ADC2EN;

	// Enable ADC - PB0: IN8; PB1: IN9; PA1: IN1; PA2: IN2; PA3: IN3; PC0: IN10, PC2: IN12, PC4: IN14; PA7: IN7, PC1: IN11
	GPIOB->MODER |= GPIO_MODER_MODER0;				// Set PB0 to Analog mode (0b11)
	GPIOB->MODER |= GPIO_MODER_MODER1;				// Set PB1 to Analog mode (0b11)
	GPIOA->MODER |= GPIO_MODER_MODER1;				// Set PA1 to Analog mode (0b11)
	GPIOA->MODER |= GPIO_MODER_MODER2;				// Set PA2 to Analog mode (0b11)
	GPIOA->MODER |= GPIO_MODER_MODER3;				// Set PA3 to Analog mode (0b11)
	GPIOC->MODER |= GPIO_MODER_MODER0;				// Set PC0 to Analog mode (0b11)
	GPIOC->MODER |= GPIO_MODER_MODER2;				// Set PC2 to Analog mode (0b11)
	GPIOC->MODER |= GPIO_MODER_MODER4;				// Set PC4 to Analog mode (0b11)
	GPIOA->MODER |= GPIO_MODER_MODER7;				// Set PA7 to Analog mode (0b11)
	GPIOC->MODER |= GPIO_MODER_MODER1;				// Set PA7 to Analog mode (0b11)

	ADC2->CR1 |= ADC_CR1_SCAN;						// Activate scan mode
	ADC2->SQR1 = (ADC_BUFFER_LENGTH - 1) << 20;		// Number of conversions in sequence
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
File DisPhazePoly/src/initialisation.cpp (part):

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{
	InitClocks();
	InitSysTick();
	InitDAC();						// DAC1 Output on PA4 (Pin 20); DAC2 Output on PA5 (Pin 21)
	InitADC();						// Configure ADC for analog controls
	InitDebugTimer();				// Timer to check available calculation time
	InitPWMTimer();					// PWM timers for LED control
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
void InitDAC()
{
	// Once the DAC channelx is enabled, the corresponding GPIO pin (PA4 or PA5) is automatically connected to the analog converter output (DAC_OUTx).
	// In order to avoid parasitic consumption, the PA4 or PA5 pin should first be configured to analog (AIN).

	// Enable DAC and GPIO Clock
	RCC->AHB1ENR |= RCC_AHB1ENR_GPIOAEN;			// Enable GPIO Clock
	RCC->APB1ENR |= RCC_APB1ENR_DACEN;				// Enable DAC Clock

	DAC->CR |= DAC_CR_EN1;							// Enable DAC using PA4 (DAC_OUT1)
	DAC->CR &= ~DAC_CR_BOFF1;						// Enable DAC channel output buffer to reduce the output impedance
	DAC->CR |= DAC_CR_TEN1;							// DAC 1 enable trigger - allows samples to be loaded into DAC then sent on interrupt
	DAC->CR |= DAC_CR_TSEL1;						// Set trigger to software (0b111: Software trigger)

	DAC->CR |= DAC_CR_EN2;							// Enable DAC using PA5 (DAC_OUT2)
	DAC->CR &= ~DAC_CR_BOFF2;						// Enable DAC channel output buffer
	DAC->CR |= DAC_CR_TEN2;							// DAC 2 enable trigger
	DAC->CR |= DAC_CR_TSEL2;						// Set trigger to software (0b111: Software trigger)
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	RCC->AHB1ENR |= RCC_AHB1ENR_GPIOAEN | RCC_AHB1ENR_GPIOBEN | RCC_AHB1ENR_GPIOCEN;
	RCC->APB2ENR |= RCC_APB2ENR_ADC1EN;

	GPIOA->MODER |= GPIO_MODER_MODER1 | GPIO_MODER_MODER2 | GPIO_MODER_MODER3 | GPIO_MODER_MODER7;		// Configure PA1 (1), PA2 (2), PA3 (3) PA7 (7) to Analog mode (0b11)
	GPIOB->MODER |= GPIO_MODER_MODER0 | GPIO_MODER_MODER1;		// Configure PB0 (8), PB1 (9) to Analog mode (0b11)
	GPIOC->MODER |= GPIO_MODER_MODER0 | GPIO_MODER_MODER1 | GPIO_MODER_MODER2 | GPIO_MODER_MODER4;	// Configure PC0 (10), PC1 (11), PC2 (12), PC4 (14) to Analog mode (0b11)

	ADC1->CR1 |= ADC_CR1_SCAN;						// Activate scan mode
	ADC1->SQR1 = (ADC_BUFFER_LENGTH - 1) << ADC_SQR1_L_Pos;		// Number of conversions in sequence
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	RCC->AHB1ENR |= RCC_AHB1ENR_GPIOCEN;
	RCC->APB2ENR |= RCC_APB2ENR_ADC2EN;

	// Enable ADC - PB0: IN8; PB1: IN9; PA1: IN1; PA2: IN2; PA3: IN3; PC0: IN10, PC2: IN12, PC4: IN14; PA7: IN7, PC1: IN11
	GPIOB->MODER |= GPIO_MODER_MODER0;				// Set PB0 to Analog mode (0b11)
	GPIOB->MODER |= GPIO_MODER_MODER1;				// Set PB1 to Analog mode (0b11)
	GPIOA->MODER |= GPIO_MODER_MODER1;				// Set PA1 to Analog mode (0b11)
	GPIOA->MODER |= GPIO_MODER_MODER2;				// Set PA2 to Analog mode (0b11)
	GPIOA->MODER |= GPIO_MODER_MODER3;				// Set PA3 to Analog mode (0b11)
	GPIOC->MODER |= GPIO_MODER_MODER0;				// Set PC0 to Analog mode (0b11)
	GPIOC->MODER |= GPIO_MODER_MODER2;				// Set PC2 to Analog mode (0b11)
	GPIOC->MODER |= GPIO_MODER_MODER4;				// Set PC4 to Analog mode (0b11)
	GPIOA->MODER |= GPIO_MODER_MODER7;				// Set PA7 to Analog mode (0b11)
	GPIOC->MODER |= GPIO_MODER_MODER1;				// Set PA7 to Analog mode (0b11)

	ADC2->CR1 |= ADC_CR1_SCAN;						// Activate scan mode
	ADC2->SQR1 = (ADC_BUFFER_LENGTH - 1) << 20;		// Number of conversions in sequence
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
void InitPWMTimer()
{
	// Red LED: PB3 (TIM2 CH2); Green LED: PB7 (TIM4 CH2)
	RCC->AHB1ENR |= RCC_AHB1ENR_GPIOBEN;
	RCC->APB1ENR |= RCC_APB1ENR_TIM2EN | RCC_APB1ENR_TIM4EN;

	// Enable channel 2 PWM output pins on PB3
	GPIOB->MODER &= ~(GPIO_MODER_MODE3_0 | GPIO_MODER_MODE7_0);			// 00: Input mode; 01: General purpose output mode; 10: Alternate function mode; 11: Analog mode (default)
	GPIOB->MODER |= GPIO_MODER_MODE3_1 | GPIO_MODER_MODE7_1;
	GPIOB->AFR[0] |= GPIO_AFRL_AFSEL3_0;			// Timer 2 Output channel is AF1
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	// ARR = number of counts per PWM tick = 4096
	// 33.6m / ARR = 8.2kHz of PWM square wave with 4096 levels of output

	// Red LED: PB3 (TIM2 CH2)
	TIM2->CCMR1 |= TIM_CCMR1_OC2PE;					// Output compare 2 preload enable
	TIM2->CCMR1 |= (TIM_CCMR1_OC2M_1 | TIM_CCMR1_OC2M_2);	// 0110: PWM mode 1 - In upcounting, channel 2 active if TIMx_CNT<TIMx_CCR2
	TIM2->CCR2 = 0x0;								// Initialise PWM level
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	TIM2->EGR |= TIM_EGR_UG;						// 1: Re-initialize the counter and generates an update of the registers
	TIM2->CR1 |= TIM_CR1_CEN;						// Enable counter

	// Green LED: PB7 (TIM4 CH2)
	TIM4->CCMR1 |= TIM_CCMR1_OC2PE;					// Output compare 2 preload enable
	TIM4->CCMR1 |= (TIM_CCMR1_OC2M_1 | TIM_CCMR1_OC2M_2);	// 0110: PWM mode 1 - In upcounting, channel 2 active if TIMx_CNT<TIMx_CCR2
	TIM4->CCR2 = 0x0;								// Initialise PWM level
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{
	RCC->APB1ENR |= RCC_APB1ENR_UART4EN;			// UART4 clock enable

	GpioPin::Init(GPIOC, 11, GpioPin::Type::AlternateFunction, 8);	// PC11 UART4_RX

	int Baud = (SystemCoreClock / 4) / (16 * 31250);
	UART4->BRR |= Baud << 4;						// Baud Rate (called USART_BRR_DIV_Mantissa) = (Sys Clock: 168MHz / APB1 Prescaler DIV4: 42MHz) / (16 * 31250) = 84
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
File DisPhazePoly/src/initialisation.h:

#pragma once

#include "stm32f4xx.h"
#include <cstring>
#include "GpioPin.h"

static constexpr uint32_t sampleRateMono = 88000;
static constexpr uint32_t sampleRatePoly = 66000;

#define PITCH_SPREAD -583.0f
static constexpr float PITCH_OFFSET = 1129.5f;

static constexpr uint32_t sysTickInterval = 1000;
extern uint32_t SystemCoreClock;
extern volatile uint32_t SysTickVal;

static constexpr uint32_t adcMax = 4095;
#define ADC_BUFFER_LENGTH 10

#define FFT_ANALYSIS false

struct ADCValues {
	uint16_t Pitch_CV; 	// PB0 ADC12_IN8   Pin 27
	uint16_t VCA;     	// PA3 ADC123_IN3  Pin 17
	uint16_t FTune;   	// PC4 ADC12_IN14  Pin 24
	uint16_t CTune;   	// PB1 ADC12_IN9   Pin 26
	uint16_t Osc1Type;	// PC1 ADC12_IN11  Pin 9
	uint16_t Osc2Type;	// PA2 ADC123_IN2  Pin 16
	uint16_t PD1CV;   	// PC2 ADC123_IN12 Pin 10
	uint16_t PD2CV;   	// PA1 ADC123_IN1  Pin 15
	uint16_t PD1Pot;  	// PA7 ADC12_IN7   Pin 23
	uint16_t PD2Pot;  	// PC0 ADC123_IN10 Pin 8
};

extern volatile ADCValues adc;

extern GpioPin debugPin;


void InitHardware();
void InitClocks();
void InitSysTick();
void InitDAC();
void InitGPIO();
void InitSampleTimer();
void InitADC();
void InitDebugTimer();
void InitPWMTimer();
void InitMidiUART();
void DelayMS(uint32_t ms);
void JumpToBootloader();

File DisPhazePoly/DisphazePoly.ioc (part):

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Mcu.Name=STM32F405RGTx
Mcu.Package=LQFP64
Mcu.UserName=STM32F405RGTx
PA11.Mode=Device_Only
PA11.Signal=USB_OTG_FS_DM
PA12.Mode=Device_Only
PA12.Signal=USB_OTG_FS_DP
PA9.Mode=Activate_VBUS
PA9.Signal=USB_OTG_FS_VBUS
PH0-OSC_IN.Mode=HSE-External-Oscillator
PH0-OSC_IN.Signal=RCC_OSC_IN
PH1-OSC_OUT.Mode=HSE-External-Oscillator
PH1-OSC_OUT.Signal=RCC_OSC_OUT
RCC.HSE_VALUE=12000000
RCC.SYSCLKFreq_VALUE=168000000
RCC.SYSCLKSource=RCC_SYSCLKSOURCE_PLLCLK
board=custom
